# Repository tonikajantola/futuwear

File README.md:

Futuwear - the posture-tracking smart shirt project
================

Contents
----------------
* **Blender/** 3D visualization source files (for web UI)
* **pcb/** Printed circuit board design
* **server/** Server front & back end, API use simulations
* **src/** Source code of firmware and desktop client

Usage
================

Client
----------------
Power on the device, and run **src/python-bluetooth/rfcomm-client.py** with python.

Server
----------------
See Readme inside **/server/**.

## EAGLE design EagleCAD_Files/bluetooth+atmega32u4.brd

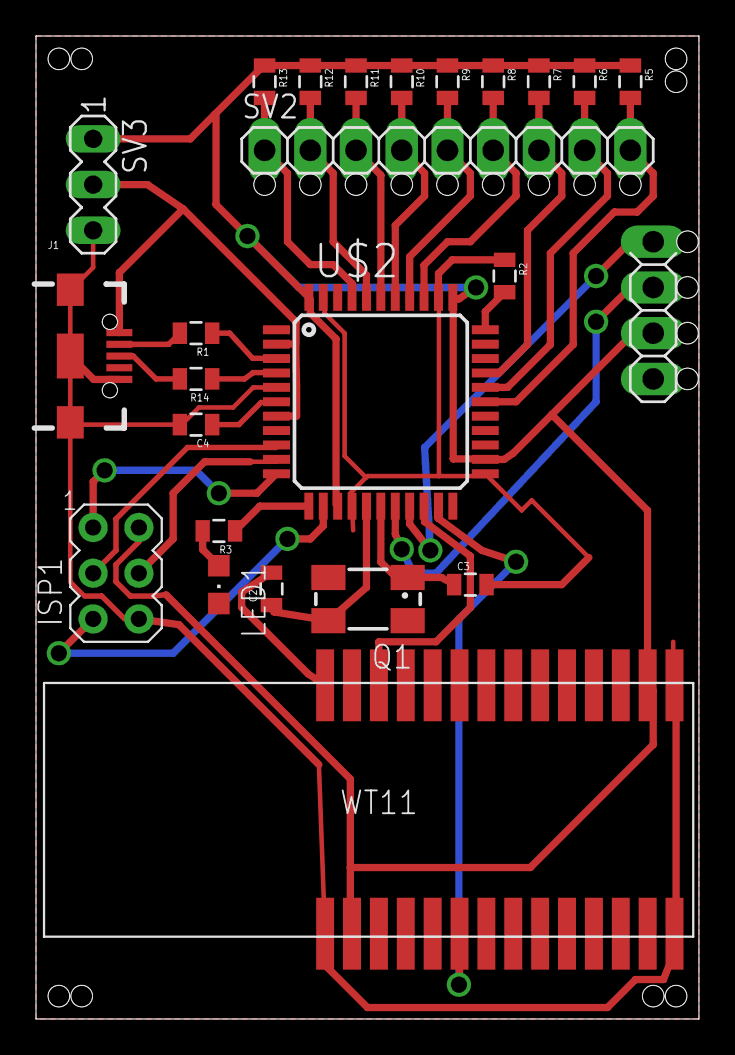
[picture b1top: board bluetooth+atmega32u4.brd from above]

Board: 2 copper layers, 36.8 x 54.6 mm, 24 parts (0 on the bottom side), 30 nets.

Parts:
C2, C3: 22pF; 0805
C4: 1µF; 0805
ISP1: AVRISP-6; AVRISP
J1: USB-B-MICRO-SMD_V03
LED1: CHIPLED_0805
Q1: 16MHz; CTS406
R1, R14: 22R; 0805
R2: 10k; 0805
R3: 470R; 0805
R5, R6, R7, R8, R9, R10, R11, R12, R13: 1k; 0805
SV2: 1X13-WEARABLE
SV3: MA03-1
U$2: ATMEGA32U4-AU; TQFP44
WT11: BLUEGIGAWT11-LONG-PADS; BLUEGIGAWT11-LONGPADS

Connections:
3V3: ISP1.2, R5.1, R6.1, R7.1, R8.1, R9.1, R10.1, R11.1, R12.1, R13.1, SV2.12, SV3.1, U$2.14, U$2.24, U$2.34, U$2.44, WT11.2, WT11.16
ANALOG1: R13.2, SV2.1, U$2.41
ANALOG2: R12.2, SV2.2, U$2.40
ANALOG3: R11.2, SV2.3, U$2.39
ANALOG4: R10.2, SV2.4, U$2.38
ANALOG5: R9.2, SV2.5, U$2.37
ANALOG6: R8.2, SV2.6, U$2.36
ANALOG7: R7.2, SV2.7, U$2.30
ANALOG8: R6.2, SV2.8, U$2.29
ANALOG9: R5.2, SV2.9, U$2.28
GND: C2.2, C3.2, C4.2, ISP1.6, J1.GND, J1.SHIELD1, J1.SHIELD2, J1.SHIELD3, LED1.C, R2.1, SV2.13, SV3.3, U$2.5, U$2.15, U$2.23, U$2.35, U$2.43, WT11.1, WT11.14, WT11.15, WT11.28
LED: R3.1, U$2.12
MISO: ISP1.1, U$2.11
MOSI: ISP1.4, U$2.10
unnamed: C3.1, Q1.1, U$2.17
unnamed: C2.1, Q1.3, U$2.16
unnamed: C4.1, U$2.6
unnamed: R1.1, U$2.3
unnamed: R14.1, U$2.4
unnamed: J1.D+, R14.2
unnamed: J1.D-, R1.2
unnamed: R2.2, U$2.33
unnamed: LED1.A, R3.2
RESET: ISP1.5, U$2.13
RXD: U$2.20, WT11.26
SCK: ISP1.3, U$2.9
SCL: SV2.11, U$2.18
SDA: SV2.10, U$2.19
TXD: U$2.21, WT11.6
USB5V: J1.VBUS, SV3.2, U$2.2, U$2.7

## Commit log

2016-06-09 init
2016-06-13 Muokkastesti
2016-06-13 testi
2016-06-13 Implemented Node.js server, saves JSON POSTs to file
2016-06-13 testailua
2016-06-13 Added run instructions and save timestamps
2016-06-13 Added bootstrap
2016-06-15 Blender-filut
    Eka testi
2016-06-15 Blender-luusto
    Ykisttäisen luun kierto armaturessa sekä sensorin min ja max arvoja käsittelevää matematiikkaa.
2016-06-15 Added a basic sensor view
2016-06-16 nodemcu now creates json packages
2016-06-16 Pushing mocked client
2016-06-16 Improved frame rate settings for data visualizer + simple noise suppression for analog readings in Arduino
2016-06-16 3D Torso lisätty
    Arnold sekä luusto valmiina toimintaan.
2016-06-16 Changed UI port to 80
2016-06-16 Port tweaks
2016-06-16 Bicep-action
    Nyt haba kasvaa kättä taittaessa.
2016-06-17 Implemented a stub sensor to work through Vör
2016-06-20 Bluetooth example code, fixed to work with Uno
2016-06-20 Testitiedosto monen sensorin lukuun
2016-06-20 More blender test code
2016-06-20 Front-end tweaks
2016-06-20 Test UI improvements
2016-06-20 Finished test UI
2016-06-21 Visualisation improvements
2016-06-21 Working analog sensor data upload test from NodeMCU to Vör
2016-06-21 Rendering fixed
    Torso now renders correctly in the game engine.
2016-06-22 Game Engine Problem Solving
    Created one instance where bones move. Not implemented for the real rig yet. Problem seems to be in mesh modifiers.
2016-06-22 Sensor map
2016-06-22 Map range tweaks
2016-06-22 Debugging Elmo
2016-06-22 Average removal
2016-06-22 Inverted visualisation
2016-06-22 3D Works in real time now
    Can now take readings from a flex sensor and convert them into shoulder movement on the x-axis.
2016-06-22 Bluetooth communication with JSON output, with memory issues
2016-06-22 Bluetooth JSON sensor dump now working; fixed out-of-memory issues
2016-06-24 Switched to ArduinoJSON, use hardware serial with WT11
2016-06-24 Spew data across resets, info about dependencies
2016-06-26 Bluetooth communication + JSON parsing test with Blender
2016-06-27 Testing out SQL
2016-06-27 Bluetooth plotting
2016-06-27 Siistitty blend-file
    Pohja Blend4Webiin siirtymistä varten
2016-06-28 Attempting MySQL integration
2016-06-28 Fixed initial SQL integration
2016-06-28 Removed illegal token
2016-06-28 SQL saving mechanism
2016-06-28 Database entry fixes
2016-06-29 Testing chart.js
2016-06-29 Modified SQL query to display per-second average
2016-06-29 Plotting fixes
2016-06-29 Timestamp fixes
2016-06-29 Blend4Web Start
    Luiden liikuttamisen mysteeri avattu onnistuneesti sekä logic nodejen toimintaa selvitetty ja käytetty. Raakaversio serverin kanssa kommunikoivasta node-setupista asetettu paikoilleen.
2016-06-29 Blend4Web
    Alexin haltuun
2016-06-29 Blend4Web2
    Alex2
2016-06-29 Blend4Web3
    Alex3
2016-06-29 Testing blender node JS callbacks
2016-06-29 improved plotter
2016-06-29 copied simple line buffering to rfcomm-client
2016-06-29 Blend4Web
    Alkukantainen node-setup sekä kaikki emptyt ohjaamassa luita.
2016-06-29 UI changes
2016-06-29 Blend4Web
    Ei ei ei ei....
2016-06-29 changed JSON format, lots of effort
2016-06-29 Set up BT/python script for testing
2016-06-30 Fixed bluetooth relay
2016-06-30 Tried an md5 auth
2016-06-30 MD5 fixes
2016-06-30 Added hash test to posting
2016-06-30 Hash debug
2016-06-30 Delegated DB conn strings
2016-06-30 Node db string fixed
2016-06-30 Notepad++
2016-06-30 Recalled how JS functions work
2016-07-03 JSON-Success
    Javascriptissä annettu custom komento "rotval" antaa nyt arvonsa blenderin puolelle.
2016-07-04 Blend4web server setup
2016-07-04 Blender web integration, mysql tweaks
2016-07-04 Fixed db connection
2016-07-04 Fixed false-valued db insertion
2016-07-04 Blend4Web
    Käsien rotaatio asetettu halutulle välille
2016-07-04 Cleaned up server directory
2016-07-04 Changed sensor scale to 0-1000
2016-07-05 Switch to Teensy 2.0, updated plotter's json parsing
2016-07-05 3D Rotations changed into parent-axis
    Nyt luut voivat pyöriä keskenään nätisti.
2016-07-05 Added more rotation options for bones
    Process is moving slowly
2016-07-06 Shoulder-test
    Bluetoothilla testaamista varten. Oikea olkapää liikkuu lähetetyn datan tahdissa.
2016-07-06 fixed a steaming shitload of broken stuff, with love
2016-07-06 Set up comms between root and torso iframe
2016-07-06 unified bluetooth handling in python scripts
2016-07-06 3D Rotation command overhaul
    Vanha logic nodeihin perustuva logiikka heitetty pois ja siirrytty JS-muotoisiin rotate käskyihin, joilla voi operoida suoraan luita.
2016-07-07 Device auth setup
2016-07-07 Node syntax fixes
2016-07-07 Fixed devauth
2016-07-11 Android client initial commit
2016-07-11 Disabling bluetooth and returning to app prompts bluetooth enable screen
2016-07-11 Android-studio "Before Commit [x] Reformat Code" test
2016-07-11 list paired devices
2016-07-11 Fixed 3D rotation and implemented sensor reading to rotations
    Alex <3
2016-07-12 re-added android-client
2016-07-12 code styling
2016-07-12 code styling test
2016-07-12 one more code styling test
2016-07-12 button works now (small steps! :D)
2016-07-12 xml formatting
2016-07-12 bluetooth server socket opens now but BluetoothServerSocket.accept() does not work yet
2016-07-13 Assistant comments
2016-07-13 Revert "Merge branch 'master' of ssh://github.com/EinoVirtanen/futuwear"
    This reverts commit d9e6e070b3abeac144715b81d713b8d99e9afaac, reversing
    changes made to df490da3b629810082347921461cdb4cc65909b5.
2016-07-13 Torso takaisin
2016-07-13 Torson luut nimetty taas
    Alex <3<3
2016-07-13 Uusi yritys...
2016-07-13 Torso.js formatting
2016-07-13 android client reinit
2016-07-13 android client test commit
2016-07-13 performed Gradle clean
2016-07-13 Kolmas kerta toden sanoo
2016-07-13 bluetooth accept timeout was 30ms instead of 30s
2016-07-13 Updated sensor config UI
2016-07-13 Fixed mysql fail callback
2016-07-13 Syntax fixes
2016-07-13 Implemented sensor registration
2016-07-13 Fixed sensor+data join
2016-07-13 Added logging to cookie lookup
2016-07-13 Fixed multi-sensor support
2016-07-13 Added string fixes (mysql)
2016-07-13 bluetooth adapter and device work
2016-07-13 Differentiated between sensor ID and name
2016-07-13 Fixed syntax
2016-07-14 Accelerometer-koodi lisätty
2016-07-14 Began to round out UI
2016-07-14 UI Dial tweaks
2016-07-14 UI tweaks
2016-07-14 Fixed sensor adding
2016-07-15 Added request data to fetch method
2016-07-16 Fixed cookie adding
2016-07-18 Torso is now well lit and the skin color is changed
2016-07-18 Torso lighting 2.0
2016-07-18 Partitioned UI root into two interfaces
2016-07-18 Added more info to history UI
2016-07-18 Fixed archived data view
2016-07-19 Changes that should've been on git ages ago
2016-07-19 Torso stomach growth implemented
2016-07-19 All bugs in torso growth are now fixed
2016-07-20 Made the sample size which controls shape key easier to modify.
    Pause between samples is still to be implemented.
2016-07-20 Time window moved.
    Time window is now between the samples rather than after both have been taken. Should be more logical to use.
2016-07-20 Server-ready version
    Unnecessary things commed out. Take it from here Alex <3
2016-07-20 Slider tweaks
2016-07-20 Torso json for stomach
2016-07-20 Unified visualisation
2016-07-20 Fixed int parsing in UI
2016-07-20 Debugging UI
2016-07-20 Teensy now generates a permanent UUID for identification
2016-07-20 Added datapoint visualisation
2016-07-20 Added a function to update sensor values with gyro.
2016-07-20 Fixed slider alignment
2016-07-20 Reverted torso
2016-07-20 Reverted torso.blend and updated torso.js
    Torso.js now features a function to update with accelerometer data.
2016-07-20 Stomach action (peck destroyed)
2016-07-20 Server-ready torso.js
2016-07-21 Set up a notification system
2016-07-21 Further fixes
2016-07-21 Fixed manage.html
2016-07-25 Socketio server-client dualism
2016-07-25 Corrected socketio management
2016-07-25 Fixed socket pathways
2016-07-25 Added test notification
2016-07-25 Dix attmepts
2016-07-25 Fixed UI stuff
2016-07-25 Fixed socket.id multiple adding
2016-07-25 Improvements and comments in firmware, setup for fresh WT11 on PCB
2016-07-25 Added analyzation
2016-07-25 Brushed up notification display
2016-07-25 Tried to fix notification dismissing
2016-07-25 Fixed scope issues
2016-07-25 Added debug lines
2016-07-25 Fixed inner join
2016-07-27 Eagle Cad files added
    Everything required to start printing out the boards.
2016-07-27 Switched to UUID-central authentication
2016-07-27 Acquire_fat virtaviivaistettu
    Laihtumisen säätäminen on nyt helpompaa uudella variablella slim_multiplier
2016-07-27 Brushed up UUID-auth, UI tweaks
2016-07-28 Torso.js siistitty ja englanninnettu
    Ich sprache Englisch
2016-07-28 Made realtime view comply with UUID-centricity
2016-07-28 32u4 chip now works properly.
2016-07-29 LED blinking, lots of debugging and crashing, broken right now
2016-07-31 Firmware now provides uuid, pin and name upon client's request.
2016-07-31 Code documentation, directory organizing
2016-08-01 Minor text fixes
2016-08-01 sensor_update_gyro rename to sensor_update_accelerometer
    Better in line with what the actual sensor is.
2016-08-01 Fixed multi-device view
2016-08-01 Client now sends device name
2016-08-01 Fixed manage page
2016-08-03 Fixed discarding
2016-08-04 Pin mappings for shirt, tuned up python code
2016-08-04 pressure sensor support, puppeling, plotter now works (poorly)
2016-08-04 sensor inversions + autorange exceptions
2016-08-07 Implemented triggered sensor warnings
2016-08-07 Code legibility tweaks
2016-08-07 Final file arrangements
2016-08-07 Removed JSON debugging box
2016-08-19 Create LICENCE

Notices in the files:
parts and their libraries:
SparkFun-Capacitors: Licensing: Creative Commons ShareAlike 4.0 International - https://creativecommons.org/licenses/by-sa/4.0
